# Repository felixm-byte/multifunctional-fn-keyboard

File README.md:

# multifunctional-fn-keyboard
A function keyboard that is also a retro-style game controller. Switch modes, display button mappings or (soon) cool graphics on the colour display, and connect to any USB device. Includes accelerometer/gyroscope for natural-feeling motion controls in games.

Schematic diagram showing the wiring of pins on the Pi Pico.

## Inspiration
I've always thought a little remappable keyboard would be super useful for input in DIY projects, to easily test USB input, and I love the GameCube controller's middle screen and wanted to design games around it, so I decided to build this project to combine those 2 goals. Once I build the physical model, I will test out multi-key input for deeper shortcuts within apps, to make it also work as a function keyboard. I also have a built-in accelerometer/gyroscope, which will make for fun features and interactions in games and potentially also for software shortcuts.

# Design note
The controller works better without button-caps since the buttons can be directly exposed. This means I need one less part and one less supplier, making the design cheaper and simpler, and it is fine to expose buttons directly from the PCB, which is done in products like Hack Club Sprig.

# Parts
- Display: [ST7735 LCD display from Aliexpress, "1.8 TFT NO TOUCH" version](https://www.aliexpress.com/item/4000219159401.html)
- Microcontroller: Pi Pico 2 (definitely compatible with 2W, probably also with original series Picos)
- Refer to [ibom.html](design/bom/ibom.html) for interactive bill of materials 
- all other parts listed with LCSC part numbers in design/production/bom.csv
- PCB parts: £14.70 (backorder or JLCPCB idle parts) + £3 (display + screws)
- 3D printed parts
- 4xM3 16mm [(pan-head) screws with nyloc ends](https://www.aliexpress.com/item/1005012276006033.html)
- I have included a seperate document with links (bom-links.csv) for ease of purchasing, but it is probably best to get all parts except the Pi Pico using the JLCPCB assembly service.
- Total part cost: ~£18 (excluding PCB production and case 3D printing)

# Renders

For demonstration only - colour and look will vary based on PCB manufacturing and colour used.

# Details
- Runs on MicroPython - you need to [install this on the Pi Pico](https://www.raspberrypi.com/documentation/microcontrollers/micropython.html) before installing main.py, mappings.kb and gamepad_mappings.kb (the content of the mappings files can be the same, but you need one mappings.kb and one gamepad_mappings.kb for the firmware to run)  
- Uses basic USB keyboard inputs (currently - additional feature implementation in progress) so universally compatible with devices supporting USB HID
- Designed in KiCad (PCB) and [OnShape (case) - click to open source files](https://cad.onshape.com/documents/51850c34b98423dfb69681d3/w/19fcd9cddc7b2960ac2d3a69/e/14cd91361d094cded8dbd10b?renderMode=0&uiState=69dd64714df5b6410170c326), use these programs to open or edit.

# Setup guide
- Get together all of the parts listed in the parts list (the 3D-printed shell is optional but strongly recommended for safety and comfort).
- To get all of the parts I will manufacture the PCB using a service like JLCPCB using the Gerber source file (design/gerber.zip), purchase parts using the bom.csv file which can be uploaded directly to LCSC for convenience. It could be more cost-effective to buy a Pi Pico 2 from a local source than LCSC. I would recommend you do something similar.
- Solder on all parts as shown in diagrams, including the Pi Pico (2) which should be soldered onto the PCB. The soldering should be moderate/medium difficulty, but I have not assembled it yet myself. Alternatively, use a PCB-assembly service like JLCPCB (notes in PCB assembly section).
- (optional) design/production/case-(bottom/top).stl are the 3D printing file for the case. 3D print the case in 2 seperate parts and use M3 16mm screws and nyloc nuts to attach it to the PCB, by placing the PCB into the slots in the bottom (larger) part of the case, inserting the screws through from the bottom, placing the top part of the case (which has cross cutouts for the button layouts) above the PCB and using the nyloc part to secure the screws from the top.
- (optional) Set up a custom .kb mappings file using the setup.py tool, ensure it is named mappings.kb or gamepad_mappings.kb for its use.
- Install main.py along with required micropython libraries (from external libraries section of readme), and .kb files, to the Pico.
- Connect to the device via USB. Press one button along with the HELP button to see what a button is mapped to. Hold down the 1,2,3,4&5 buttons simultaneously to switch from gamepad to keyboard mode (this leads to changed latencies for the specific use).

# PCB assembly
- If you would prefer not to assemble the PCB by hand, I would recommend using a PCB assembly service, especially for the small parts that can be placed cheaply by this service.
- I made an effort to minimise the number of parts used that are outside the JLCPCB basic library, so that the model can be assembled affordably using the JLCPCB PCBA service, which charges a US$3 fee per JLCPCB 'extended' part used.
- Some parts like the Pi Pico itself are non-machine-solderable (JLCPCB charges much extra for them) so I would recommend soldering them yourself, but you can pay the extended manufacturing surcharge and a series of $3 'extended parts' fees to have it fully assembled if that suits you better.
- Please let me know if there are any JLCPCB basic parts that could be used as substitutes so I can integrate them into the design, but I have looked quite deeply into this so I doubt there are any.
- I have chosen the B3F-4000 switches because of their much greater number of cycles (3 million vs 100 thousand) which is important for a keyboard that would be used regularly. Feel free to substitute this to suit your usecase.

# References
- https://www.youtube.com/watch?v=KaGHxvVnKQ4 (1:24 for display pinout explanation)
- https://github.com/alastairhm/micropython-st7735 for MicroPython display driver - this library needs to be installed on the Pi Pico
- https://github.com/micropython/micropython-lib/tree/master/micropython/usb -  MicroPython HID implementation
- https://cad.onshape.com/documents/51850c34b98423dfb69681d3/w/19fcd9cddc7b2960ac2d3a69/e/14cd91361d094cded8dbd10b?renderMode=0&uiState=69dd64714df5b6410170c326 OnShape source files

# External libraries
- https://github.com/alastairhm/micropython-st7735/tree/main - SPI TFT with ST7735 Driver library for Raspberry Pi Pico Micropython
- https://how2electronics.com/interfacing-mpu6050-with-raspberry-pi-pico-micropython/ - simple SPI driver for mpu6050 gyroscope

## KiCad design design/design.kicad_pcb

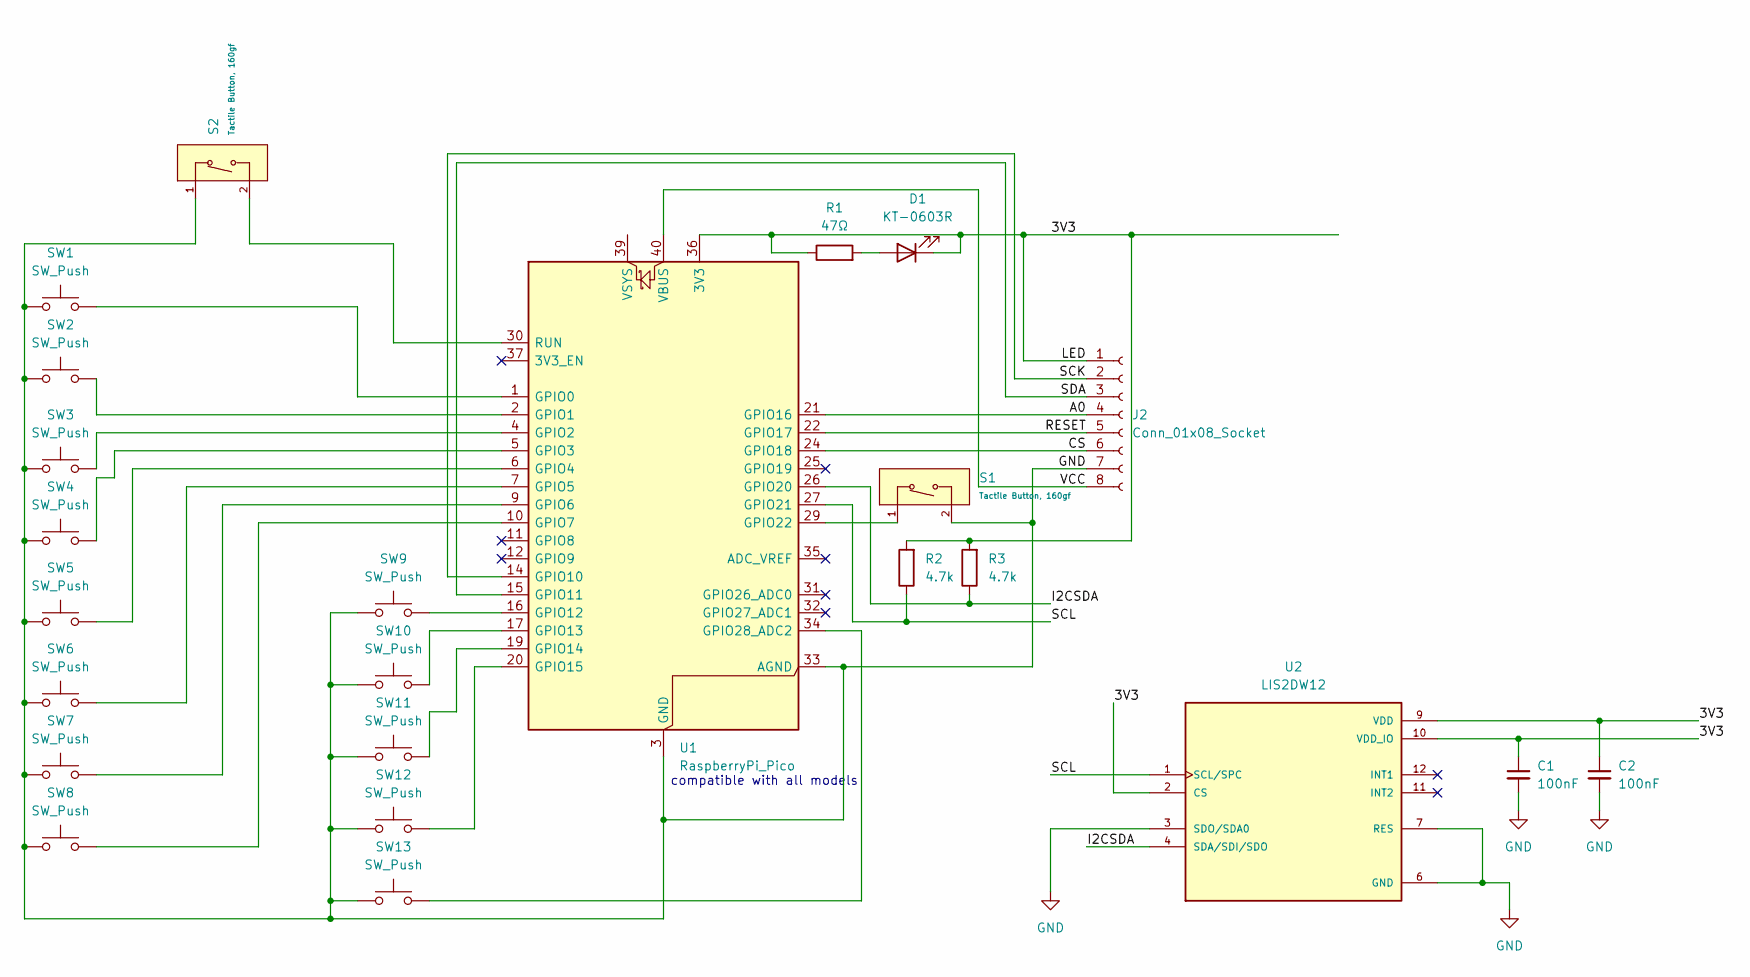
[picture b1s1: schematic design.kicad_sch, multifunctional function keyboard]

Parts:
C1, C2: 100nF; C_0402_1005Metric; LCSC C307331
D1: KT-0603R; LED_0603_1608Metric; LCSC C2286
J2: Conn_01x08_Socket; PinSocket_1x08_P2.54mm_Vertical; LCSC C27438
R1: 47Ω; R_0201_0603Metric; LCSC C23182
R2, R3: 4.7k; R_0603_1608Metric; LCSC C23162
S1, S2: Tactile Button, 160gf; SW_TS-1088-AR02016; Voltage Rating (Dc) 12V; Part TS-1088-AR02016; LCSC C720477
SW1, SW2, SW3, SW4, SW5, SW6, SW7, SW8, SW9, SW10, SW11, SW12, SW13: SW_Push; SW_SPST_Omron_B3F-40xx; LCSC C87494
U1: RaspberryPi_Pico; RaspberryPi_Pico_Common_Unspecified; LCSC C41407547
U2: LIS2DW12; LGA12R50P4X4_200X200X70; PARTREV 4; LCSC C50385411

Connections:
/3V3: C1.1, C2.1, D1.1 (K), J2.1, R1.1, R2.2, R3.2, U1.36 (3V3), U2.2 (CS), U2.9 (VDD), U2.10 (VDD_IO)
/A0: J2.4, U1.21 (GPIO16)
/CS: J2.6, U1.24 (GPIO18)
/I2CSDA: R3.1, U1.26 (GPIO20), U2.4 (SDA/SDI/SDO)
/RESET: J2.5, U1.22 (GPIO17)
/SCK: J2.2, U1.14 (GPIO10)
/SCL: R2.1, U1.27 (GPIO21), U2.1 (SCL/SPC)
/SDA: J2.3, U1.15 (GPIO11)
/VCC: J2.8, U1.40 (VBUS)
GND: C1.2, C2.2, J2.7, S1.2 (B), S2.1 (A), SW1.2, SW2.2, SW3.2, SW4.2, SW5.2, SW6.2, SW7.2, SW8.2, SW9.2, SW10.2, SW11.2, SW12.2, SW13.2, U1.3 (GND), U1.8 (GND), U1.13 (GND), U1.18 (GND), U1.23 (GND), U1.28 (GND), U1.33 (AGND), U1.38 (GND), U2.3 (SDO/SDA0), U2.6 (GND), U2.7 (RES), U2.8 (GND)
unnamed: D1.2 (A), R1.2
unnamed: S1.1 (A), U1.29 (GPIO22)
unnamed: S2.2 (B), U1.30 (RUN)
unnamed: SW1.1, U1.1 (GPIO0)
unnamed: SW2.1, U1.2 (GPIO1)
unnamed: SW3.1, U1.4 (GPIO2)
unnamed: SW4.1, U1.5 (GPIO3)
unnamed: SW5.1, U1.6 (GPIO4)
unnamed: SW6.1, U1.7 (GPIO5)
unnamed: SW7.1, U1.9 (GPIO6)
unnamed: SW8.1, U1.10 (GPIO7)
unnamed: SW9.1, U1.16 (GPIO12)
unnamed: SW10.1, U1.17 (GPIO13)
unnamed: SW11.1, U1.19 (GPIO14)
unnamed: SW12.1, U1.20 (GPIO15)
unnamed: SW13.1, U1.34 (GPIO28_ADC2)

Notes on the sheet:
compatible with all models

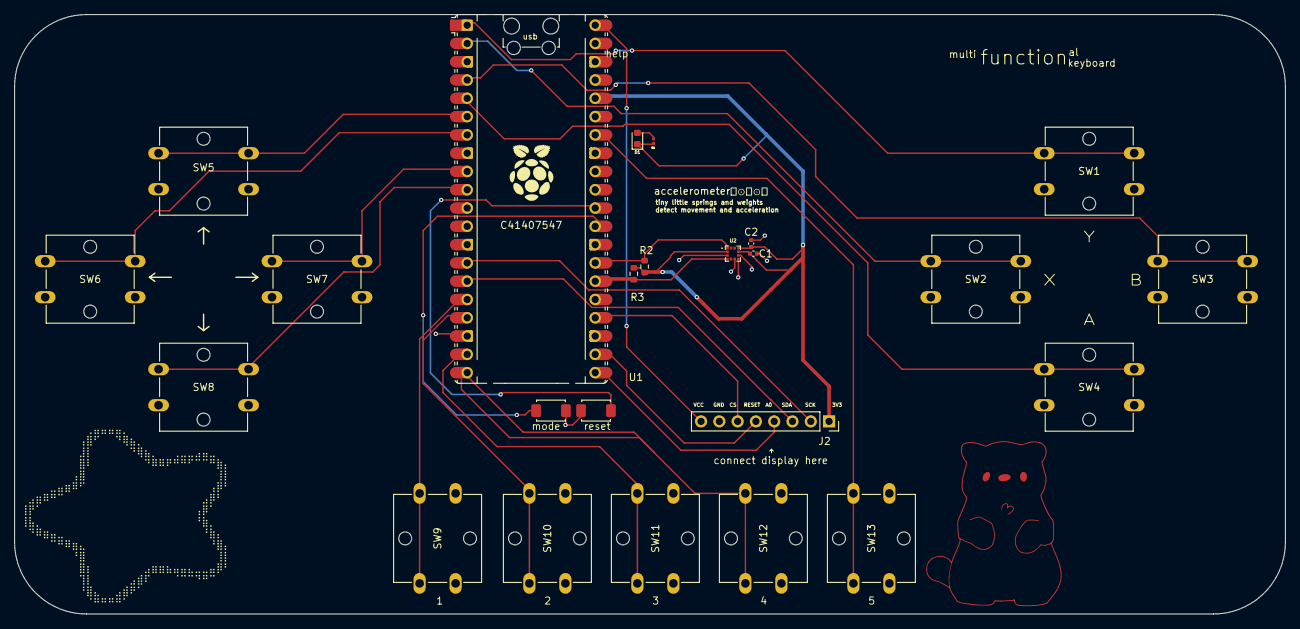
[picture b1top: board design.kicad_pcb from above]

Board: 2 copper layers, 176.5 x 83.2 mm, 24 parts (0 on the bottom side), 26 nets.

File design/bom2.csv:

"Id";"Designator";"Footprint";"Quantity";"Designation";"Supplier and ref";
1;"A1";"RaspberryPi_Pico_Common_Unspecified";1;"RaspberryPi_Pico";;;
2;"D1";"LED_0603_1608Metric";1;"KT-0603R";;;
3;"J2, J2";"PinSocket_1x08_P2.54mm_Vertical";2;"Conn_01x08_Socket";;;
4;"R1";"R_0201_0603Metric";1;"47Ω";;;
5;"S1, S2";"SW_TS-1088-AR02016";2;"Tactile Button, 160gf";;;
6;"SW1, SW2, SW3, SW4, SW5, SW6, SW7, SW8, SW9, SW10, SW11, SW12, SW13";"SW_SPST_Omron_B3F-40xx";13;"SW_Push";;;

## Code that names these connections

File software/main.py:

import usb.device
from usb.device.keyboard import KeyboardInterface, KeyCode, LEDCode
from machine import Pin,SPI,I2C
import time
import pickle
from st7735 import TFT
from st7735 import sysfont
import math
import _thread
import gc
import mpu6050 as gyro

i2c_gyro = I2C(0, scl=Pin(21), sda=Pin(20), freq=400000)
spi = SPI(1, baudrate=20000000, polarity=0, phase=0, sck=Pin(10), mosi=Pin(11), miso=None) #mosi is the same as SDA
tft=TFT(spi,16,17,18)
tft.initr()
tft.rgb(True)


KEYS = (
    (Pin.CPU.GPIO0, "Y"),
    (Pin.CPU.GPIO1, "X"),
    (Pin.CPU.GPIO2, "B"),
    (Pin.CPU.GPIO3, "A"),
    (Pin.CPU.GPIO4, "UP"),
    (Pin.CPU.GPIO5, "LEFT"),
    (Pin.CPU.GPIO6, "RIGHT"),
    (Pin.CPU.GPIO7, "DOWN"),
    (Pin.CPU.GPIO12, "1"),
    (Pin.CPU.GPIO13, "2"),
    (Pin.CPU.GPIO14, "3"),
    (Pin.CPU.GPIO15, "4"),
    (Pin.CPU.GPIO28, "5")
) # verify with hardware, layout may change before production

#in this design the only LED is power, power is not connected to a GPIO pin

#the device has 2 modes - gamepad and function keyboard
#in function keyboard mode, people will not want signals to be sent multiple times even if they hold down the button - simplistic debouncing by giving a 1000ms wait until button is sent again
#in gamepad, people will want to hold down a button or mash repeatedly so a very short debouncing time should be used (20ms)
#the shortcut to switch to/from gamepad is holding down 1,2,3,4,5 simultaneously, which is almost impossible to fat finger but easy and memorable to do
REFRESH_TIME = 5
#bouncing times must be a multiple
GAMEPAD_BOUNCING_TIME = 20
KEYBOARD_BOUNCING_TIME = 1000

help_button = Pin.CPU.GPIO22
help_button.init(Pin.IN, Pin.PULL_UP)

for pin, _ in KEYS:
    pin.init(Pin.IN, Pin.PULL_UP)

class Keyboard(KeyboardInterface):
    pass #there is no custom keyboard functionality needed right now, change if needed in future

gamepad_mode = False 
keyboard = Keyboard()
mappings = {}; gamepad_mappings = {}

def display_help(keyname, keymapping):
    tft.fill(TFT.BLACK)
    v = 30
    tft.text((0, v), f"The key {keyname}", TFT.RED, sysfont, 1, nowrap=True)
    v += sysfont["Height"]
    tft.text((0,v), f"maps to {keymapping}", TFT.BLUe, sysfont, 2, nowrap=True)
    gc.collect()

def display_change_notice(is_in_gamepad_mode):
    tft.fill(TFT.BLACK)
    v = 30
    tft.text((0, v), f"Gamepad mode:", TFT.RED, sysfont, 1, nowrap=True)
    v += sysfont["Height"]
    tft.text((0, v), f"Turned {"on" if is_in_gamepad_mode else "off"}.", TFT.RED, sysfont, 1, nowrap=True)
    gc.collect()

def load_mappings():
    global mappings
    global gamepad_mappings
    f = open("mappings.kb", 'rb')
    mappings = pickle.load(f)
    f = open("gamepad_mappings.kb", 'rb')
    gamepad_mappings = pickle.load(f)

def output_keys(ids):
    global gamepad_mode; global mappings
    keys = []
    if gamepad_mode:
        for id in ids:
            keys.append(mappings[id])
    keyboard.send_keys(keys)

usb.device.get().init(keyboard, builtin_driver=True)

previous_keys = [["none", 0], ["none, 0"]]
while True:
    if keyboard.is_open():
        keys = []
        active_keys = []
        for pin, id in KEYS:
            if not pin(): #pin must be 0 for keys to be active
                keys.append(id)
        #this may cause lag, better to cause output lag than missing keypresses
        if not help_button():
            new_thread = _thread.start_new_thread(display_help, (str(keys[0]), (gamepad_mappings if gamepad_mode else mappings)[keys[0]] ) )

        if keys == ["1", "2", "3", "4", "5"]:
            gamepad_mode = not gamepad_mode

        
        for k in range(len(previous_keys)):
            if previous_keys[k][1] + REFRESH_TIME >= (GAMEPAD_BOUNCING_TIME if gamepad_mode else KEYBOARD_BOUNCING_TIME):
                previous_keys.pop(k)
            else:
                previous_keys[k][1] += REFRESH_TIME
            
        for key_pressed in keys:
            for p in previous_keys:
                if not key_pressed == p[0]: #key has been previously pressed
                    previous_keys.append([key_pressed, 0])
                    active_keys.append(key_pressed)

        output_keys(keys)
    motion_data = gyro.get_mpu6050_data(i2c=i2c_gyro)
    print(motion_data['temp']) #later on i will write more advanced firmware to give the data back to the host computer, but for now it can just be kept.
    time.sleep_ms(REFRESH_TIME)
    


                

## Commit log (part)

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2026-04-03 Added mounting holes KiCad
2026-04-04 KiCad work, 3D modelling case
2026-04-04 Updated manufacturing files for JLCPCB
2026-04-09 Finished simple mapping code
2026-04-10 Final changes for production
2026-04-11 Update readme with screw choice
2026-04-13 Dcoumentation, improved poster, production details
2026-04-14 Reorganised file structure, interactive BOM
2026-04-14 Removed misc file, updated readme link
2026-04-27 Replaced discontinued display part
2026-05-24 Adding gyroscope, redesigning PCB
2026-06-03 Added details on parts, added gyroscope to design
2026-06-04 Design updates and add MPU6050 driver
    Update KiCad PCB, gerbers and BOM; adjust STEP/3D model coordinates and add new 3D/production STL assets. Tidy repo by updating .gitignore and adding a VSCode setting. Remove outdated production bund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
2026-06-05 Improved poster and renders, re-exported gerber file
2026-06-05 Updated readme, added BOM links
